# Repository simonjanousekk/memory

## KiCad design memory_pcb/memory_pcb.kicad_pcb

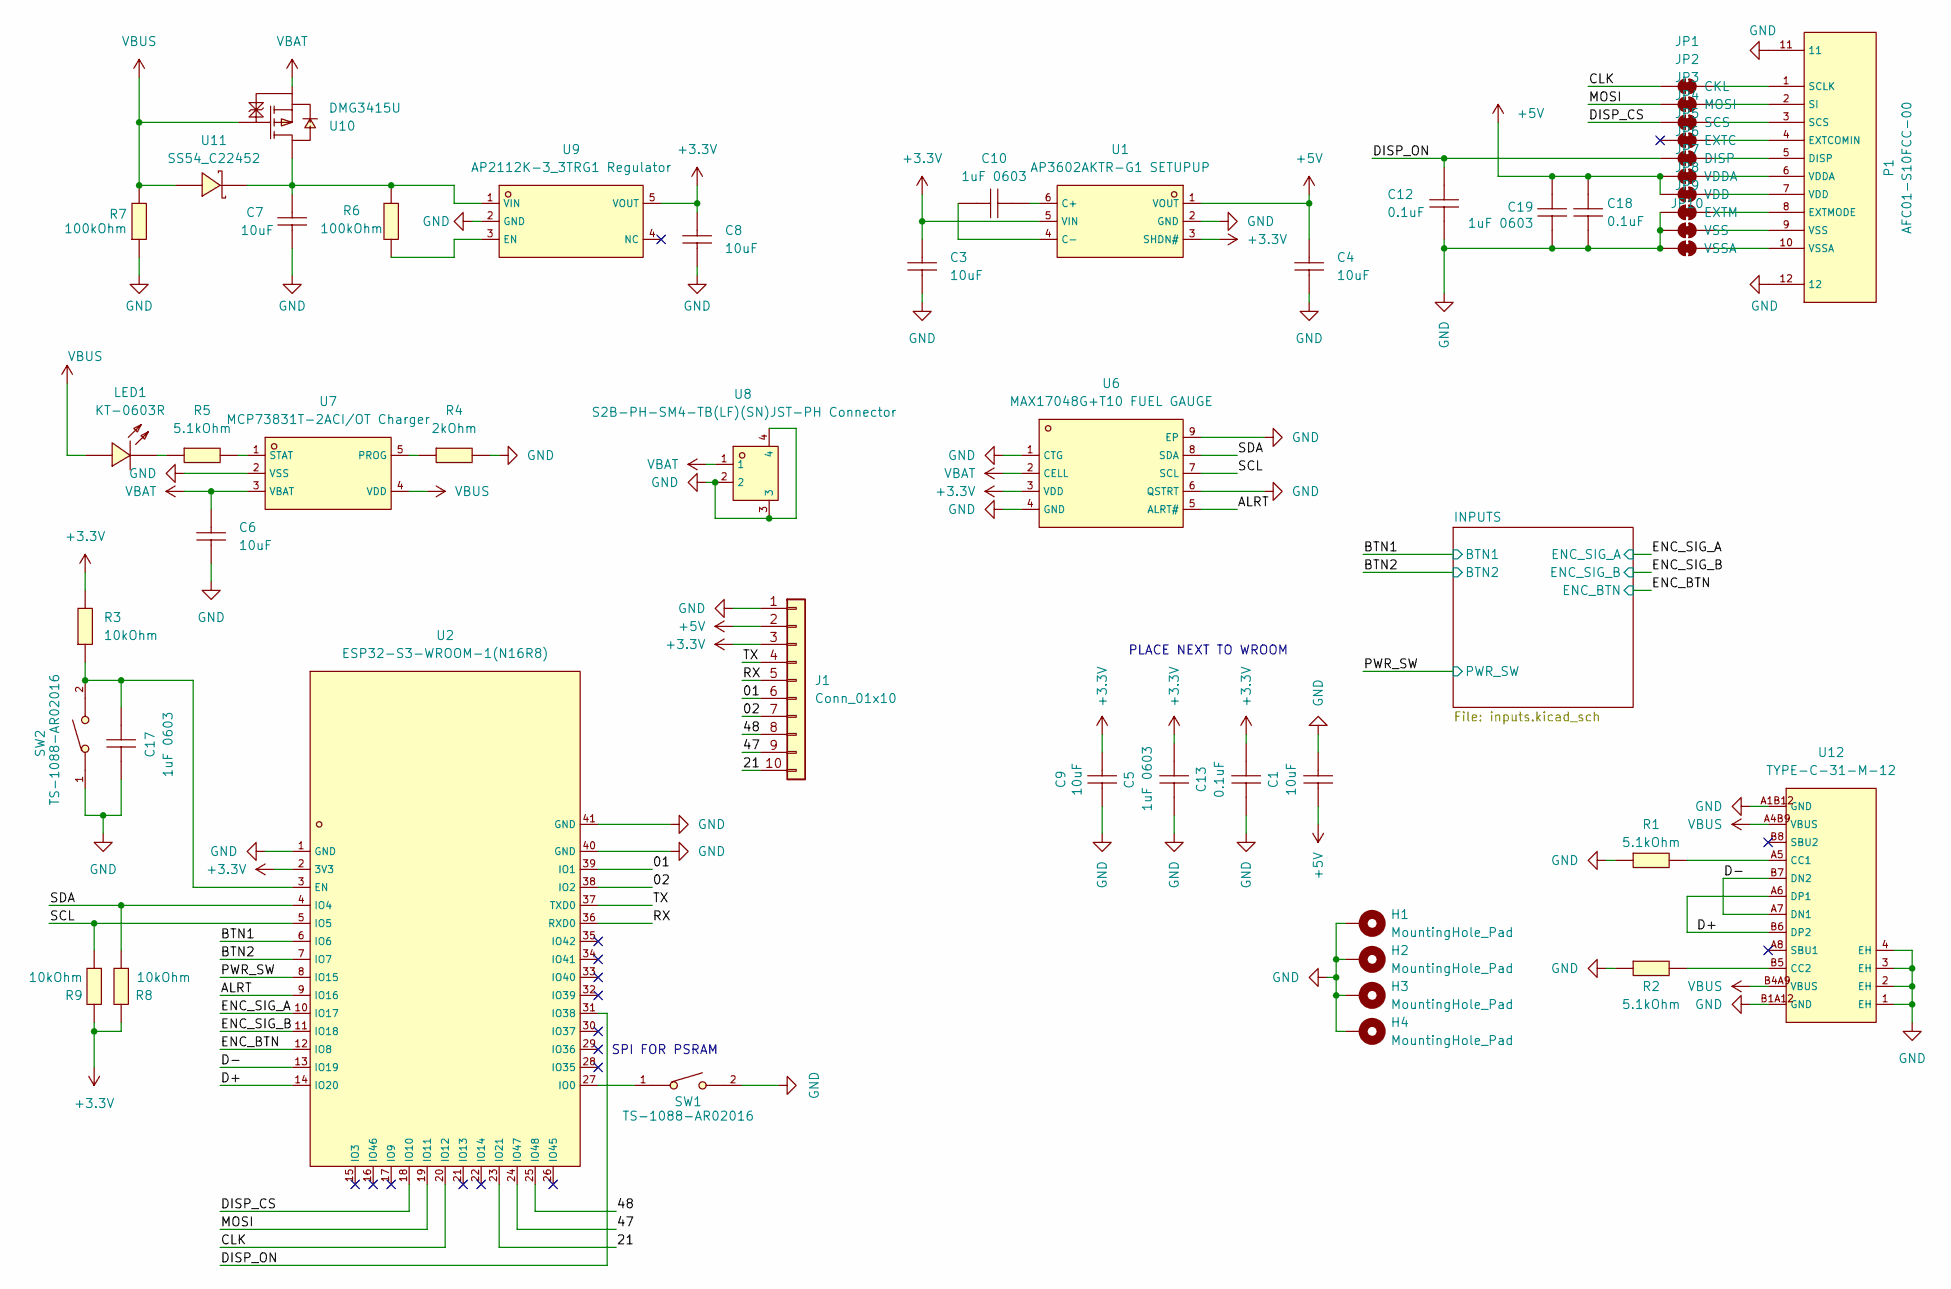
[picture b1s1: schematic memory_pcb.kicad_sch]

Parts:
C1, C3, C4, C6, C7, C8, C9: 10uF; C0402; LCSC C1523
C5, C10, C17, C19: 1uF 0603; C0603; LCSC C15849
C12, C13, C18: 0.1uF; C0402; LCSC C1525
H1, H2, H3, H4: MountingHole_Pad; MountingHole_2.2mm_M2_DIN965_Pad
J1: Conn_01x10; PinHeader_1x10_P2.54mm_Vertical
JP1: CKL; SolderJumper-2_P1.3mm_Bridged_RoundedPad1.0x1.5mm
JP2: MOSI; SolderJumper-2_P1.3mm_Bridged_RoundedPad1.0x1.5mm
JP3: SCS; SolderJumper-2_P1.3mm_Bridged_RoundedPad1.0x1.5mm
JP4: EXTC; SolderJumper-2_P1.3mm_Bridged_RoundedPad1.0x1.5mm
JP5: DISP; SolderJumper-2_P1.3mm_Bridged_RoundedPad1.0x1.5mm
JP6: VDDA; SolderJumper-2_P1.3mm_Bridged_RoundedPad1.0x1.5mm
JP7: VDD; SolderJumper-2_P1.3mm_Bridged_RoundedPad1.0x1.5mm
JP8: EXTM; SolderJumper-2_P1.3mm_Bridged_RoundedPad1.0x1.5mm
JP9: VSS; SolderJumper-2_P1.3mm_Bridged_RoundedPad1.0x1.5mm
JP10: VSSA; SolderJumper-2_P1.3mm_Bridged_RoundedPad1.0x1.5mm
LED1: KT-0603R; LED0603-RD; LCSC C2286
P1: AFC01-S10FCC-00; FPC-SMD_AFC01-S10FCC-00; LCSC C262266
R1, R2, R5: 5.1kOhm; R0603; LCSC C23186
R3, R8, R9: 10kOhm; R0603; LCSC C25804
R4: 2kOhm; R0603; LCSC C22975
R6, R7: 100kOhm; R0603; LCSC C25803
SW1, SW2: TS-1088-AR02016; SW-SMD_L3.9-W3.0-P4.45; LCSC C720477
U1: AP3602AKTR-G1 SETUPUP; SOT-23-6_L2.9-W1.6-P0.95-LS2.8-BR; LCSC C460358
U2: ESP32-S3-WROOM-1(N16R8); WIRELM-SMD_ESP32-S3-WROOM-1; LCSC C2913202
U6: MAX17048G+T10 FUEL GAUGE; TDFN-8_L2.0-W2.0-P0.50-BL-EP1.2; LCSC C2682616
U7: MCP73831T-2ACI/OT Charger; SOT-23-5_L3.0-W1.7-P0.95-LS2.8-BL; LCSC C424093
U8: S2B-PH-SM4-TB(LF)(SN)JST-PH Connector; CONN-SMD_P2.00_S2B-PH-SM4-TB-LF-SN; LCSC C295747
U9: AP2112K-3_3TRG1 Regulator; SOT-25-5_L2.9-W1.6-P0.95-LS2.8-BL; LCSC C51118
U10: DMG3415U; SOT-23-3_L2.9-W1.3-P1.90-LS2.4-BR-1; LCSC C7202986
U11: SS54_C22452; SMA_L4.4-W2.8-LS5.4-R-RD; LCSC C22452
U12: TYPE-C-31-M-12; USB-C_SMD-TYPE-C-31-M-12_1; LCSC C165948

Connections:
+3.3V: C3.2, C5.1, C8.2, C9.1, C13.2, J1.3, R3.2, R8.2, R9.2, U1.3 (SHDN#), U1.5 (VIN), U2.2 (3V3), U6.3 (VDD), U9.5 (VOUT); also elsewhere on the board
+5V: C1.1, C4.2, C18.2, C19.1, J1.2, JP6.1 (A), JP7.1 (A), U1.1 (VOUT)
/01: J1.6, U2.39 (IO1)
/02: J1.7, U2.38 (IO2)
/21: J1.10, U2.23 (IO21)
/47: J1.9, U2.24 (IO47)
/48: J1.8, U2.25 (IO48)
/ALRT: U2.9 (IO16), U6.5 (ALRT#)
/BTN1: U2.6 (IO6); also elsewhere on the board
/BTN2: U2.7 (IO7); also elsewhere on the board
/CLK: JP1.1 (A), U2.20 (IO12)
/D+: U2.14 (IO20), U12.A6 (DP1), U12.B6 (DP2)
/D-: U2.13 (IO19), U12.A7 (DN1), U12.B7 (DN2)
/DISP_CS: JP3.1 (A), U2.18 (IO10)
/DISP_ON: C12.2, JP5.1 (A), U2.31 (IO38)
/ENC_BTN: U2.12 (IO8); also elsewhere on the board
/ENC_SIG_A: U2.10 (IO17); also elsewhere on the board
/ENC_SIG_B: U2.11 (IO18); also elsewhere on the board
/MOSI: JP2.1 (A), U2.19 (IO11)
/PWR_SW: U2.8 (IO15); also elsewhere on the board
/RX: J1.5, U2.36 (RXD0)
/SCL: R9.1, U2.5 (IO5), U6.7 (SCL)
/SDA: R8.1, U2.4 (IO4), U6.8 (SDA)
/TX: J1.4, U2.37 (TXD0)
GND: C1.2, C3.1, C4.1, C5.2, C6.1, C7.1, C8.1, C9.2, C12.1, C13.1, C17.1, C18.1, C19.2, H1.1, H2.1, H3.1, H4.1, J1.1, JP8.1 (A), JP9.1 (A), JP10.1 (A), P1.11, P1.12, R1.1, R2.1, R4.2, R7.1, SW1.2, SW2.1, U1.2 (GND), U2.1 (GND), U2.40 (GND), U2.41 (GND), U6.1 (CTG), U6.4 (GND), U6.6 (QSTRT), U6.9 (EP), U7.2 (VSS), U8.2, U8.3, U8.4, U9.2 (GND), U12.1 (EH), U12.2 (EH), U12.3 (EH), U12.4 (EH), U12.A1B12 (GND), U12.B1A12 (GND); also elsewhere on the board
unnamed: JP1.2 (B), P1.1 (SCLK)
unnamed: JP2.2 (B), P1.2 (SI)
unnamed: JP3.2 (B), P1.3 (SCS)
unnamed: JP4.2 (B), P1.4 (EXTCOMIN)
unnamed: JP5.2 (B), P1.5 (DISP)
unnamed: JP6.2 (B), P1.6 (VDDA)
unnamed: JP7.2 (B), P1.7 (VDD)
unnamed: JP8.2 (B), P1.8 (EXTMODE)
unnamed: JP9.2 (B), P1.9 (VSS)
unnamed: JP10.2 (B), P1.10 (VSSA)
unnamed: LED1.1 (K), R5.1
unnamed: C10.2, U1.6 (C+)
unnamed: C10.1, U1.4 (C-)
unnamed: C17.2, R3.1, SW2.2, U2.3 (EN)
unnamed: SW1.1, U2.27 (IO0)
unnamed: R4.1, U7.5 (PROG)
unnamed: R5.2, U7.1 (STAT)
unnamed: R6.2, U9.3 (EN)
unnamed: C7.2, R6.1, U9.1 (VIN), U10.3 (D), U11.2 (K)
unnamed: R1.2, U12.A5 (CC1)
unnamed: R2.2, U12.B5 (CC2)
VBAT: C6.2, U6.2 (CELL), U7.3 (VBAT), U8.1, U10.2 (S)
VBUS: LED1.2 (A), R7.2, U7.4 (VDD), U10.1 (G), U11.1 (A), U12.A4B9 (VBUS), U12.B4A9 (VBUS)

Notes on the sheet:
SPI FOR PSRAM
PLACE NEXT TO WROOM

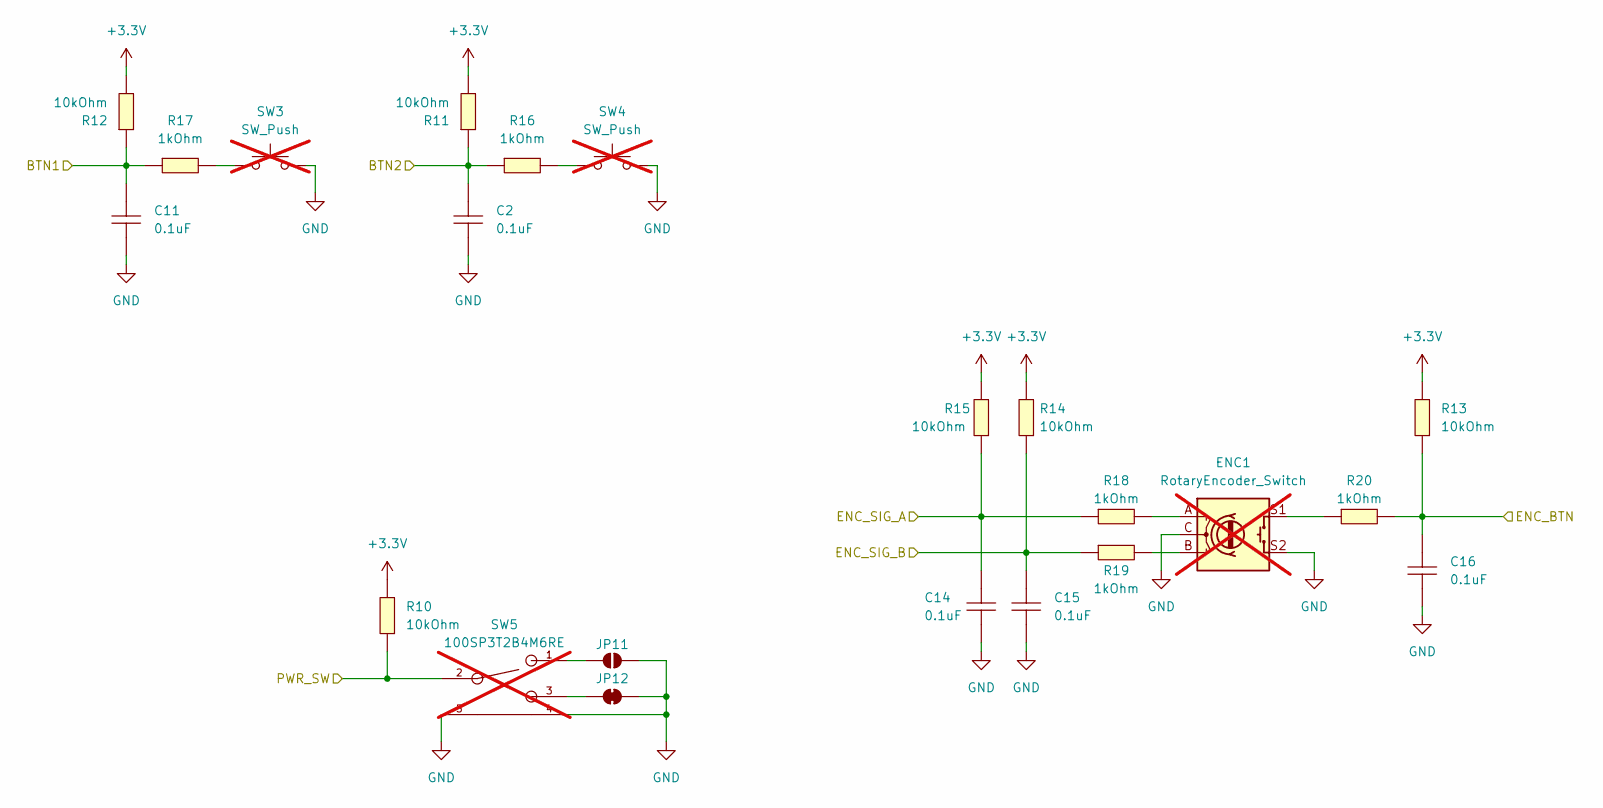
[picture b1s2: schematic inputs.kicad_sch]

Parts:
C2, C11, C14, C15, C16: 0.1uF; C0402; LCSC C1525
ENC1: RotaryEncoder_Switch; RotaryEncoder_Alps_EC11E-Switch_Vertical_H20mm; not fitted
JP11: SolderJumper_2_Open; SolderJumper-2_P1.3mm_Open_RoundedPad1.0x1.5mm
JP12: GND; SolderJumper-2_P1.3mm_Bridged_RoundedPad1.0x1.5mm
R10, R11, R12, R13, R14, R15: 10kOhm; R0603; LCSC C25804
R16, R17, R18, R19, R20: 1kOhm; R0603; LCSC C21190
SW3, SW4: SW_Push; SW_Gateron_LowProfile_THT; not fitted
SW5: 100SP3T2B4M6RE; MTS-102-C3; LCSC C273357; not fitted

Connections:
+3.3V: R10.1, R11.2, R12.2, R13.1, R14.1, R15.1; also elsewhere on the board
/BTN1: C11.2, R12.1, R17.1; also elsewhere on the board
/BTN2: C2.2, R11.1, R16.1; also elsewhere on the board
/ENC_BTN: C16.2, R13.2, R20.2; also elsewhere on the board
/ENC_SIG_A: C14.2, R15.2, R18.1; also elsewhere on the board
/ENC_SIG_B: C15.2, R14.2, R19.1; also elsewhere on the board
/PWR_SW: R10.2, SW5.2; also elsewhere on the board
GND: C2.1, C11.1, C14.1, C15.1, C16.1, ENC1.C, ENC1.S2, JP11.2 (B), JP12.2 (B), SW3.2, SW4.2, SW5.4, SW5.5; also elsewhere on the board
unnamed: ENC1.A, R18.2
unnamed: ENC1.B, R19.2
unnamed: ENC1.S1, R20.1
unnamed: JP11.1 (A), SW5.1
unnamed: JP12.1 (A), SW5.3
unnamed: R16.2, SW4.1
unnamed: R17.2, SW3.1

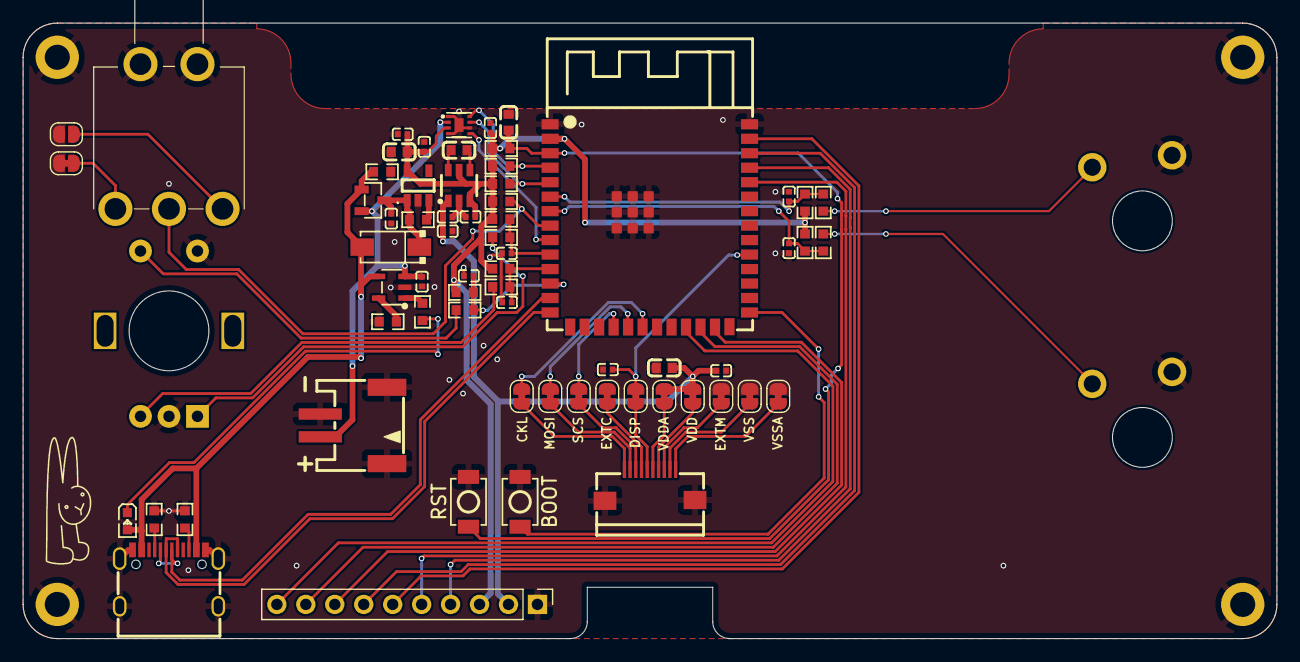
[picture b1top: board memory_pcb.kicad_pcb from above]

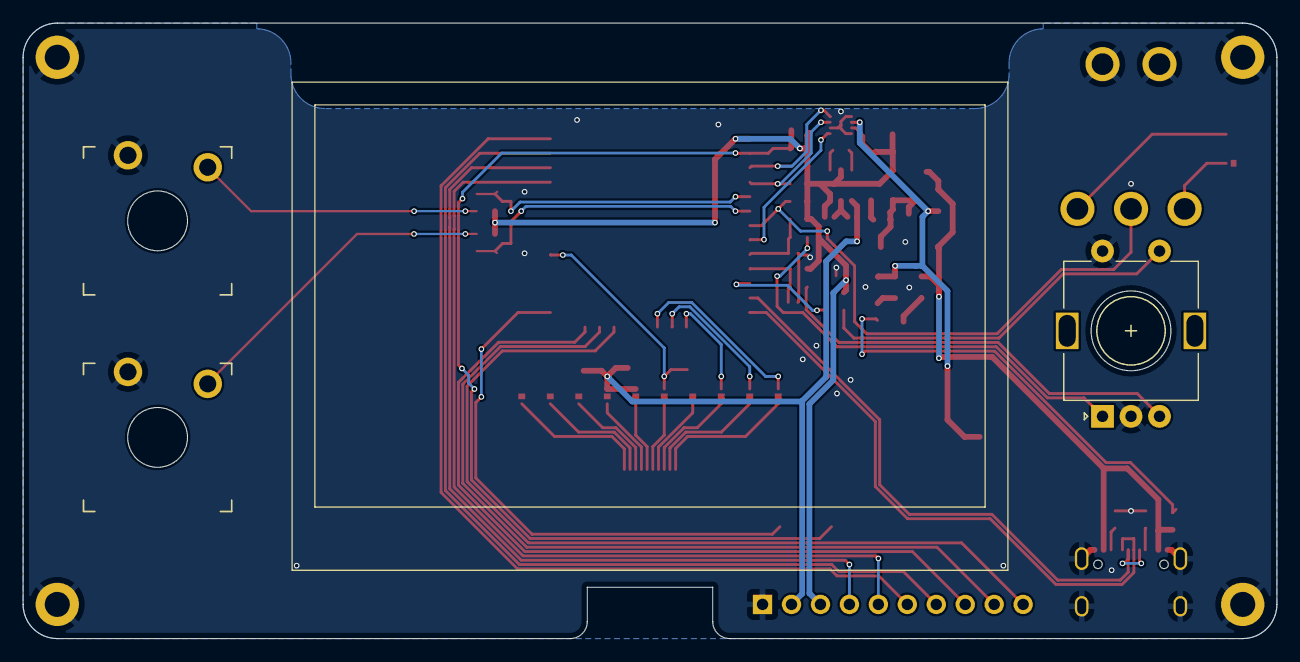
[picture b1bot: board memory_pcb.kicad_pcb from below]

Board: 2 copper layers, 110.0 x 54.0 mm, 73 parts (3 on the bottom side), 55 nets.

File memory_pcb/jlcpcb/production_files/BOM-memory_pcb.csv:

Comment,Designator,Footprint,LCSC,Quantity
0.1uF,"C11,C12,C13,C14,C15,C16,C18,C2",C0402,C1525,8
100kOhm,"R6,R7",R0603,C25803,2
10kOhm,"R10,R11,R12,R13,R14,R15,R3,R8,R9",R0603,C25804,9
10uF,"C1,C3,C4,C6,C7,C8,C9",C0402,C1523,7
1kOhm,"R16,R17,R18,R19,R20",R0603,C21190,5
1uF 0603,"C10,C17,C19,C5",C0603,C15849,4
2kOhm,R4,R0603,C22975,1
5.1kOhm,"R1,R2,R5",R0603,C23186,3
AFC01-S10FCC-00,P1,FPC-SMD_AFC01-S10FCC-00,C262266,1
AP2112K-3_3TRG1 Regulator,U9,SOT-25-5_L2.9-W1.6-P0.95-LS2.8-BL,C51118,1
AP3602AKTR-G1 SETUPUP,U1,SOT-23-6_L2.9-W1.6-P0.95-LS2.8-BR,C460358,1
DMG3415U,U10,SOT-23-3_L2.9-W1.3-P1.90-LS2.4-BR-1,C7202986,1
KT-0603R,LED1,LED0603-RD,C2286,1
MAX17048G+T10 FUEL GAUGE,U6,TDFN-8_L2.0-W2.0-P0.50-BL-EP1.2,C2682616,1
MCP73831T-2ACI/OT Charger,U7,SOT-23-5_L3.0-W1.7-P0.95-LS2.8-BL,C424093,1
S2B-PH-SM4-TB(LF)(SN)JST-PH Connector,U8,CONN-SMD_P2.00_S2B-PH-SM4-TB-LF-SN,C295747,1
SS54_C22452,U11,SMA_L4.4-W2.8-LS5.4-R-RD,C22452,1
TS-1088-AR02016,"SW1,SW2",SW-SMD_L3.9-W3.0-P4.45,C720477,2
TYPE-C-31-M-12,U12,USB-C_SMD-TYPE-C-31-M-12_1,C165948,1

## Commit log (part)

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2026-03-22 init
2026-03-22 .DS_Store remove
2026-03-23 pondeli klasika
2026-03-24 and so it begins
2026-03-25 prvni cena test
2026-03-25 uz nevim, dneska asi konec
2026-03-25 proc je tu tolik filu
2026-03-25 im sleeping
2026-03-27 looks rdy
2026-04-02 posilam
2026-04-24 step1
2026-05-02 lots of vibe coding
2026-05-03 grid testing + input overhaul
2026-05-03 sprites rename, and some junk (grid screen mostly)
2026-05-05 rename
2026-05-06 idk anymore.
2026-05-06 removal of ADAFRUIT SHARP MEM library. just adafruit GFX now.
2026-05-20 forgot about git :)
2026-05-21 nevim
2026-05-26 big vibe code incomming.
2026-05-27 webposter second commit
2026-05-27 webposter done?...?
2026-05-28 resize
